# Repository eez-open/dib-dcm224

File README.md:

### Ownership and License
The contributors are listed in CONTRIB.TXT.

Licenses | OSHWA UID
--|--
 | 

### Overview

The EEZ DIB DCM224 Power module features dual sync buck converters based on [LT3763](https://www.analog.com/en/products/lt3763.html) with programmable output voltage, PWM dimming and current limit.

### r3B2 prototype

### Feature list
- On-board STM32F373 MCU
Power input: 48 Vdc (e.g. Mean Well LRS-150F-48)
- Combined max. output power: up to 155 W
- Separate control of each power outputs
- Voltage regulation (CV), 1 – 24 V. Voltage set resolution (_U_SET_): 12-bit, read resolution (_U_MON_): 15-bit
- Current regulation (CC), up to 4.9 A. Current set resolution (_I_SET_): 12-bit, read resolution (_I_MON_): 15-bit
- PWM LED dimming
- MCU generated two counterphase switching frequencies
- On-board power pre-regulator and bias power supply
- Output Enable (_OE_) and Constant Current mode (_CC_) LED indications
- Output LC filter for improved ripple and noise
- On-board 4 mm power output terminals with standard (19.05 mm) pitch
- Pass-thru connector for Vout- coupling with other DIB power modules
- Galvanically isolated SPI bus for communication with [MCU board](https://github.com/eez-open/modular-psu/tree/master/mcu)
- I2C EEPROM for storing board specific configuration and calibration parameters
- Dimensions: 155 x 95 mm, 4-layer PCB
- **CE certified design**

### Firmware repository

https://github.com/eez-open/dib-dcm224-fw  
The firmware download procedure is described in Chapter 13.2 of the [User Manual](https://www.envox.eu/eez-bench-box-3/bb3-user-manual/13-firmware-upgrade/#bb3_man_module_upgrade).

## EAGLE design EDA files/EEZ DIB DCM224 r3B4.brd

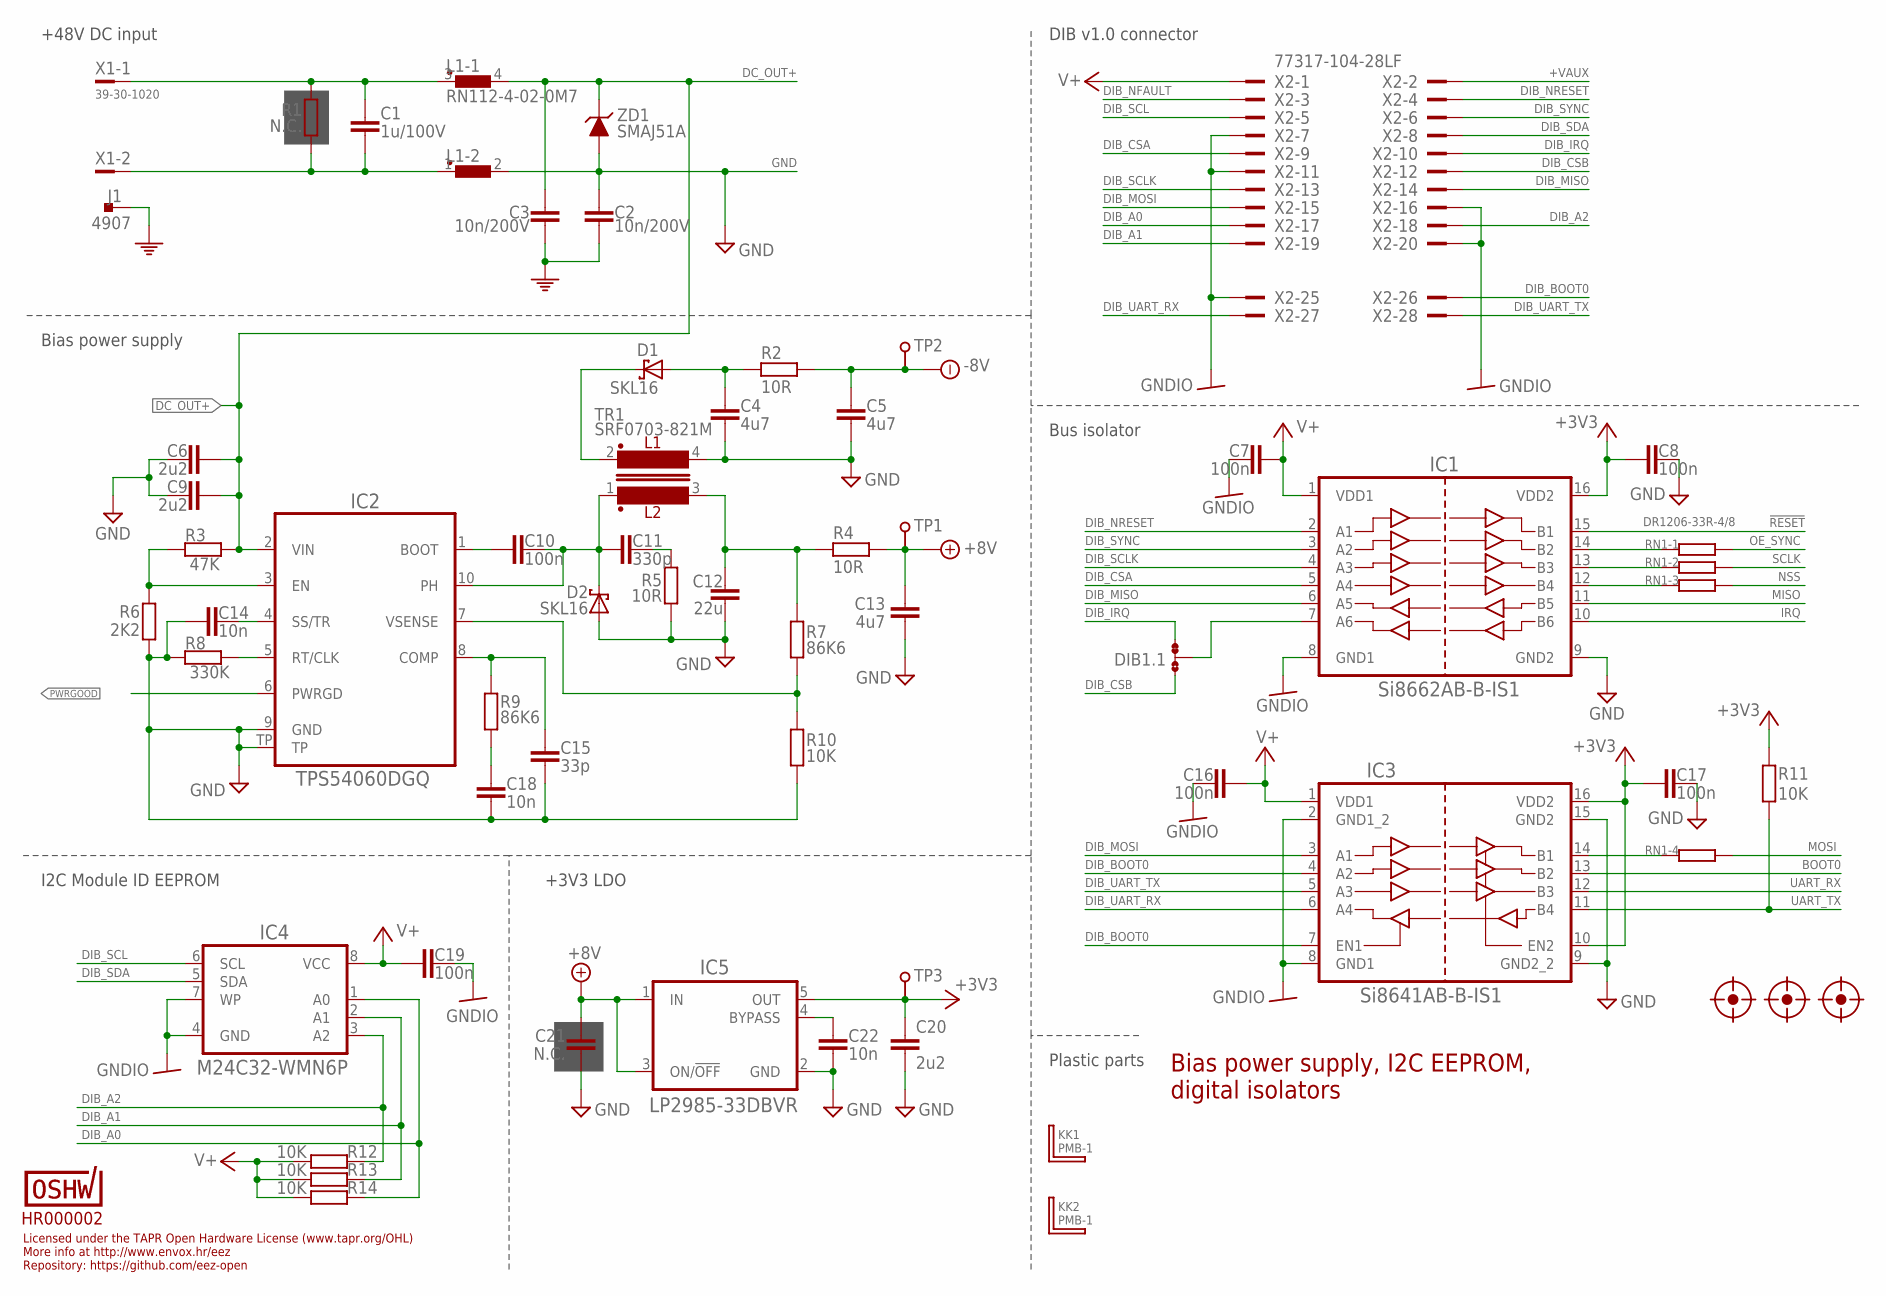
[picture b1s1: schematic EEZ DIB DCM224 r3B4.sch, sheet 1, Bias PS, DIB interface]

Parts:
C1: 1u/100V; C1206
C2, C3: 10n/200V; C1206
C4, C5, C13: 4u7; C1206
C6, C9, C20: 2u2; C1206
C7, C8, C10, C16, C17, C19: 100n; C0603
C11: 330p; C0805
C12: 22u; C1206
C14, C18, C22: 10n; C0805
C15: 33p; C0603
C21: N.C.; C0805
D1, D2: SKL16; SOD123
DIB1.1: JP3-CUT-0805-ROTATED; JP3-0805-CUT2
FM1, FM2, FM3: FIDUCIAL_2; FIDUCIAL_DUAL
IC1: Si8662AB-B-IS1; SOIC-16
IC2: TPS54060DGQ; SOP50P490X110-11N
IC3: Si8641AB-B-IS1; SOIC-16
IC4: M24C32-WMN6P; SOIC127P600X173-8N
IC5: LP2985-33DBVR; SOT95P270X145-5N
J1: 4907; PCB_TAB-4907
KK1, KK2: PMB-1; PCB-MB
L1: RN112-4-02-0M7; RN112
R1: N.C.; R2512
R2, R4, R5: 10R; R0805
R3: 47K; R0805
R6: 2K2; R0805
R7, R9: 86K6; R0805
R8: 330K; R0805
R10, R11, R12, R13, R14: 10K; R0805
RN1: DR1206-33R-4/8; CAY16
TP1, TP2, TP3: TEST-PIN_0.9MM
TR1: SRF0703-821M; SRF0703
U$1: HR000002; CERT-SMALL-SILK
X1: 39-30-1020; MINIFIT_39301020
X2: 77317-104-28LF
ZD1: SMAJ51A; DO214AA

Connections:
!RESET: IC1.15 (B1); also elsewhere on the board
+3V3: C8.2, C17.2, C20.1, IC1.16 (VDD2), IC3.10 (EN2), IC3.16 (VDD2), IC5.5 (OUT), R11.2, TP3.1; also elsewhere on the board
+8V: C13.1, C21.2, IC5.1 (IN), IC5.3 (ON/!OFF), R4.1, TP1.1; also elsewhere on the board
+VAUX: X2.2
-8V: C5.1, R2.1, TP2.1; also elsewhere on the board
BOOT0: IC3.13 (B2); also elsewhere on the board
DC+: C1.2, L1.3 (1), R1.2, X1.1
DC-: C1.1, L1.1, R1.1, X1.2
DC_OUT+: C3.2, C6.1, C9.1, IC2.2 (VIN), L1.4 (2), R3.2, ZD1.C; also elsewhere on the board
DIB_A0: IC4.1 (A0), R14.2, X2.17
DIB_A1: IC4.2 (A1), R13.2, X2.19
DIB_A2: IC4.3 (A2), R12.2, X2.18
DIB_BOOT0: IC3.4 (A2), IC3.7 (EN1), X2.26
DIB_CSA: IC1.5 (A4), X2.9
DIB_CSB: DIB1.1.NO, X2.12
DIB_IRQ: DIB1.1.NC, X2.10
DIB_MISO: IC1.6 (A5), X2.14
DIB_MOSI: IC3.3 (A1), X2.15
DIB_NFAULT: X2.3
DIB_NRESET: IC1.2 (A1), X2.4
DIB_SCL: IC4.6 (SCL), X2.5
DIB_SCLK: IC1.4 (A3), X2.13
DIB_SDA: IC4.5 (SDA), X2.8
DIB_SYNC: IC1.3 (A2), X2.6
DIB_UART_RX: IC3.6 (A4), X2.27
DIB_UART_TX: IC3.5 (A3), X2.28
GND: C2.1, C4.2, C5.2, C6.2, C8.1, C9.2, C12.2, C13.2, C14.2, C15.1, C17.1, C18.1, C20.2, C21.1, C22.1, D2.A, IC1.9 (GND2), IC2.9 (GND), IC2.TP, IC3.9 (GND2_2), IC3.15 (GND2), IC5.2 (GND), L1.2, R5.1, R6.1, R8.1, R10.1, TR1.4, ZD1.A; also elsewhere on the board
GNDIO: C7.2, C16.2, C19.1, IC1.8 (GND1), IC3.2 (GND1_2), IC3.8 (GND1), IC4.4 (GND), IC4.7 (WP), X2.7, X2.11, X2.16, X2.20, X2.25
IRQ: IC1.10 (B6); also elsewhere on the board
MISO: IC1.11 (B5); also elsewhere on the board
MOSI: RN1.5 (2); also elsewhere on the board
unnamed: IC1.14 (B2), RN1.1
unnamed: IC1.13 (B3), RN1.2 (1)
unnamed: IC1.12 (B4), RN1.3 (1)
unnamed: IC3.14 (B1), RN1.4 (1)
unnamed: C22.2, IC5.4 (BYPASS)
unnamed: C4.1, D1.A, R2.2
unnamed: C11.2, R5.2
unnamed: IC2.3 (EN), R3.1, R6.2
unnamed: C14.1, IC2.4 (SS/TR)
unnamed: IC2.5 (RT/CLK), R8.2
unnamed: C15.2, IC2.8 (COMP), R9.2
unnamed: C18.2, R9.1
unnamed: C10.2, IC2.1 (BOOT)
unnamed: IC2.7 (VSENSE), R7.1, R10.2
unnamed: DIB1.1.COM, IC1.7 (A6)
NSS: RN1.6 (2); also elsewhere on the board
OE_SYNC: RN1.8 (2); also elsewhere on the board
PE: C2.2, C3.1, J1.1, J1.2; also elsewhere on the board
PH1: C10.1, C11.1, D2.C, IC2.10 (PH), TR1.1
PWRGOOD: IC2.6 (PWRGD); also elsewhere on the board
SCLK: RN1.7 (2); also elsewhere on the board
UART_RX: IC3.12 (B3); also elsewhere on the board
UART_TX: IC3.11 (B4), R11.1; also elsewhere on the board
V+: C7.1, C16.1, C19.2, IC1.1 (VDD1), IC3.1 (VDD1), IC4.8 (VCC), R12.1, R13.1, R14.1, X2.1
VOUT+: C12.1, R4.2, R7.2, TR1.3
VOUT-: D1.C, TR1.2

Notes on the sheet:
Licensed under the TAPR Open Hardware License (www.tapr.org/OHL)
Repository: https://github.com/eez-open
More info at http://www.envox.hr/eez
I2C Module ID EEPROM
Bias power supply, I2C EEPROM, digital isolators
Plastic parts
Bus isolator
+3V3 LDO
DIB v1.0 connector
Bias power supply
+48V DC input

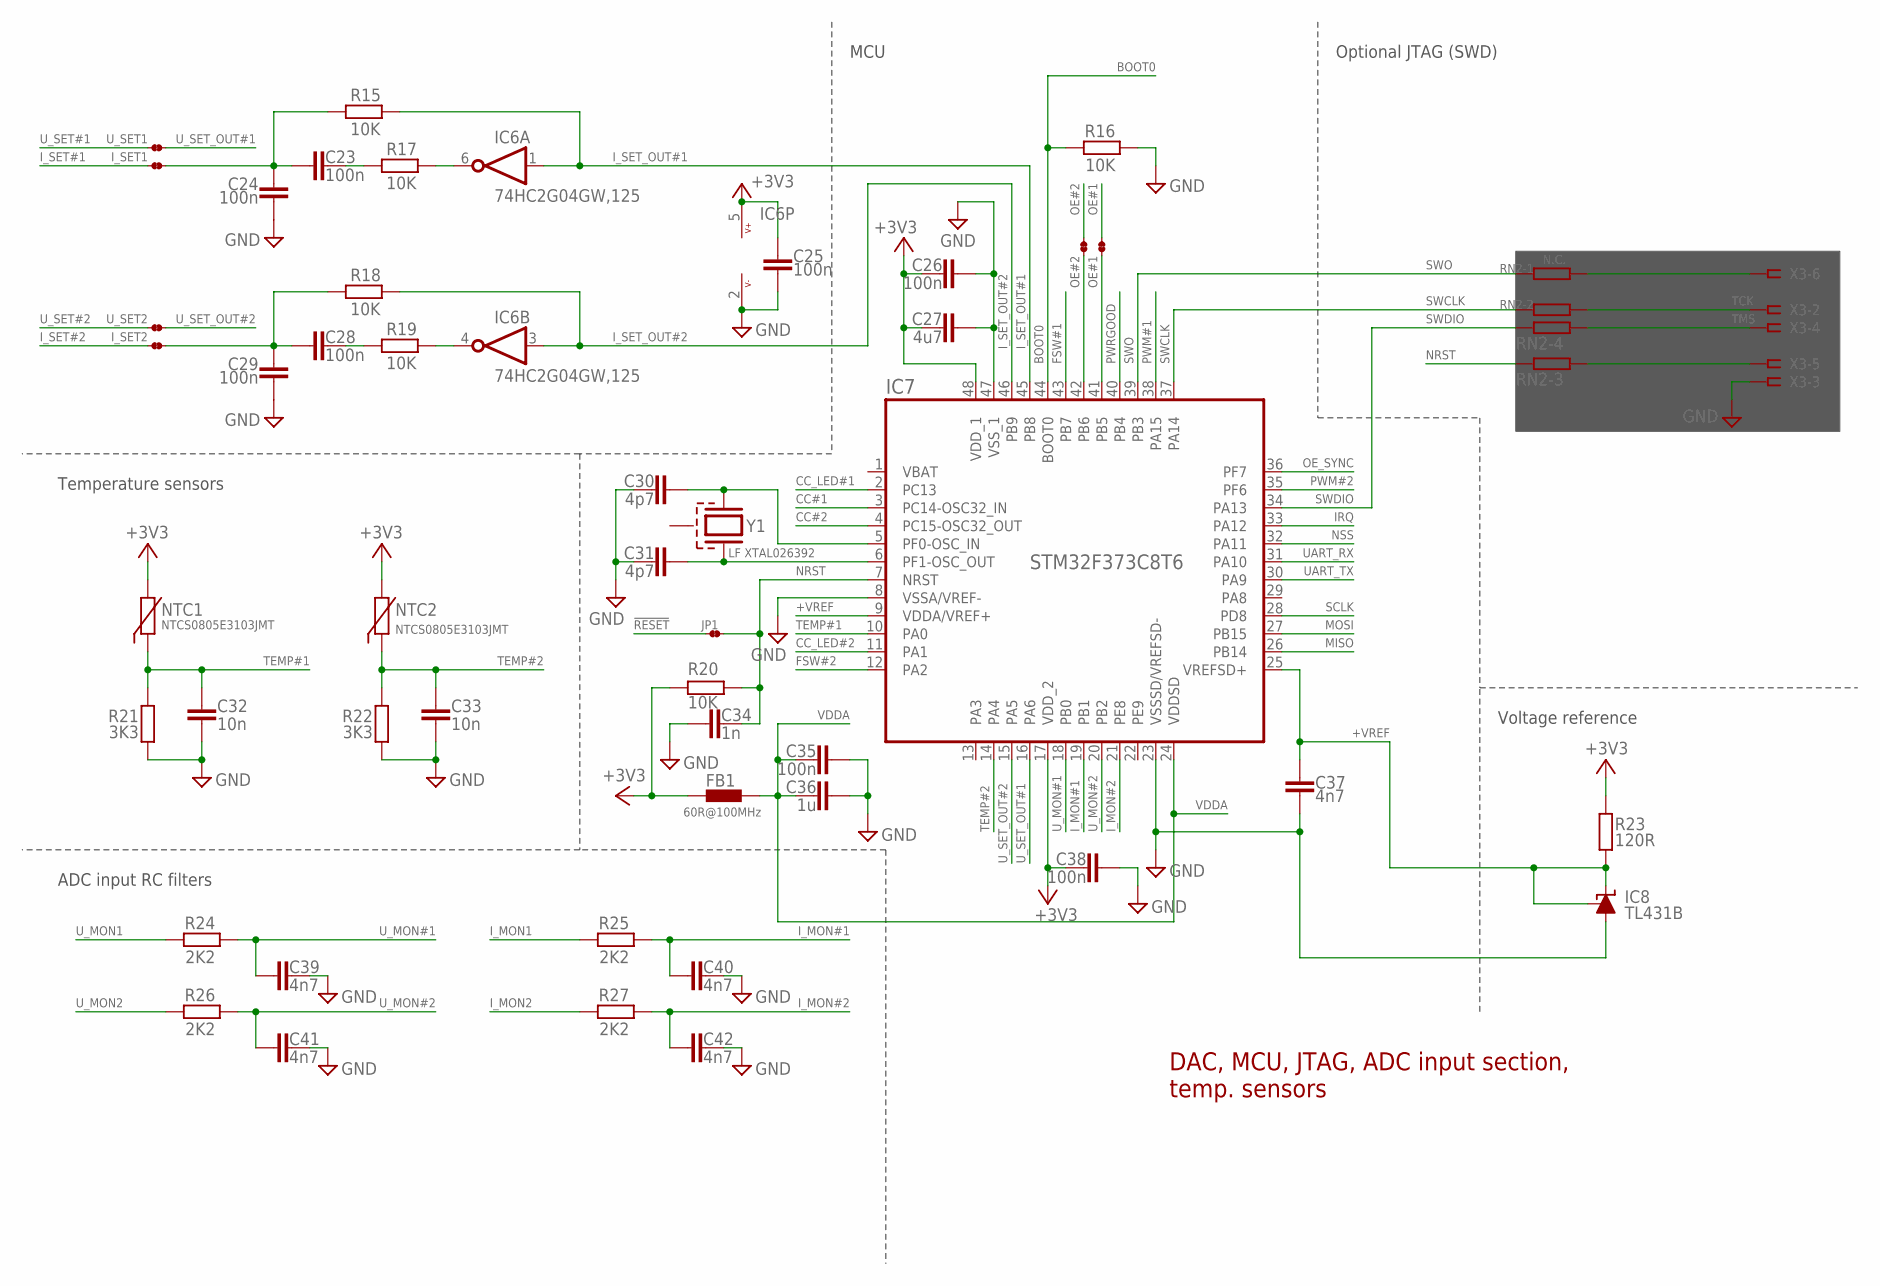
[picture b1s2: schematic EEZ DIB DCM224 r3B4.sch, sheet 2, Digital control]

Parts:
C23, C24, C25, C26, C28, C29, C35, C38: 100n; C0603
C27: 4u7; C1206
C30, C31: 4p7; C0603
C32, C33: 10n; C0805
C34: 1n; C0805
C36: 1u; C0805
C37, C39, C40, C41, C42: 4n7; C0805
FB1: 60R@100MHz; BEAD0603
IC6: 74HC2G04GW,125; SOT65P210X110-6N
IC7: STM32F373C8T6; LQFP-48
IC8: TL431B; SOT103P240X110-3N
I_SET1, I_SET2: JP2-NOCUT
JP1: JP2-NOCUT
NTC1, NTC2: NTCS0805E3103JMT; R_0805
OE#1, OE#2: JP2-NOCUT-0805; JP2-0805-NOCUT
R15, R16, R17, R18, R19, R20: 10K; R0805
R21, R22: 3K3; R0805
R23: 120R; R0805
R24, R25, R26, R27: 2K2; R0805
RN2: N.C.; CAY16
U_SET1, U_SET2: JP2-NOCUT
X3: N.C.; SSW-106-02-S-S
Y1: LF XTAL026392; 12SMX(B)

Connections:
!RESET: JP1.1; also elsewhere on the board
+3V3: C25.1, C26.2, C27.1, C38.2, FB1.P$1 (1), IC6.5 (V+), IC7.17 (VDD_2), IC7.48 (VDD_1), NTC1.1, NTC2.1, R20.1, R23.1; also elsewhere on the board
+VREF: C37.2, IC7.9 (VDDA/VREF+), IC7.25 (VREFSD+), IC8.1 (C), IC8.2 (R), R23.2
BOOT0: IC7.44 (BOOT0), R16.2; also elsewhere on the board
CC#1: IC7.3 (PC14-OSC32_IN); also elsewhere on the board
CC#2: IC7.4 (PC15-OSC32_OUT); also elsewhere on the board
CC_LED#1: IC7.2 (PC13); also elsewhere on the board
CC_LED#2: IC7.11 (PA1); also elsewhere on the board
FSW#1: IC7.43 (PB7); also elsewhere on the board
FSW#2: IC7.12 (PA2); also elsewhere on the board
GND: C24.2, C25.2, C26.1, C27.2, C29.2, C30.1, C31.1, C32.1, C33.1, C34.2, C35.1, C36.1, C37.1, C38.1, C39.1, C40.1, C41.1, C42.1, IC6.2 (V-), IC7.8 (VSSA/VREF-), IC7.23 (VSSSD/VREFSD-), IC7.47 (VSS_1), IC8.3 (A), R16.1, R21.2, R22.2, X3.3; also elsewhere on the board
IRQ: IC7.33 (PA12); also elsewhere on the board
I_MON1: R25.2; also elsewhere on the board
I_MON2: R27.2; also elsewhere on the board
I_MON#1: C40.2, IC7.19 (PB1), R25.1
I_MON#2: C42.2, IC7.21 (PE8), R27.1
I_SET#1: I_SET1.1; also elsewhere on the board
I_SET#2: I_SET2.1; also elsewhere on the board
I_SET_OUT#1: IC6.1 (I), IC7.45 (PB8), R15.2
I_SET_OUT#2: IC6.3 (I), IC7.46 (PB9), R18.2
MISO: IC7.26 (PB14); also elsewhere on the board
MOSI: IC7.27 (PB15); also elsewhere on the board
unnamed: C28.2, R19.1
unnamed: C28.1, C29.1, I_SET2.2, R18.1
unnamed: IC6.4 (O), R19.2
unnamed: RN2.8 (2), X3.6
unnamed: RN2.6 (2), X3.5
unnamed: C23.2, R17.1
unnamed: C23.1, C24.1, I_SET1.2, R15.1
unnamed: IC6.6 (O), R17.2
unnamed: IC7.42 (PB6), OE#2.1
unnamed: IC7.41 (PB5), OE#1.1
NRST: C34.1, IC7.7 (NRST), JP1.2, R20.2, RN2.3 (1)
NSS: IC7.32 (PA11); also elsewhere on the board
OE#1: OE#1.2; also elsewhere on the board
OE#2: OE#2.2; also elsewhere on the board
OE_SYNC: IC7.36 (PF7); also elsewhere on the board
PWM#1: IC7.38 (PA15); also elsewhere on the board
PWM#2: IC7.35 (PF6); also elsewhere on the board
PWRGOOD: IC7.40 (PB4); also elsewhere on the board
RCC_OSC_IN: C30.2, IC7.5 (PF0-OSC_IN), Y1.3 (2)
RCC_OSC_OUT: C31.2, IC7.6 (PF1-OSC_OUT), Y1.1
SCLK: IC7.28 (PD8); also elsewhere on the board
SWCLK: IC7.37 (PA14), RN2.2 (1)
SWDIO: IC7.34 (PA13), RN2.4 (1)
SWO: IC7.39 (PB3), RN2.1
TCK: RN2.7 (2), X3.2
TEMP#1: C32.2, IC7.10 (PA0), NTC1.2, R21.1
TEMP#2: C33.2, IC7.14 (PA4), NTC2.2, R22.1
TMS: RN2.5 (2), X3.4
UART_RX: IC7.31 (PA10); also elsewhere on the board
UART_TX: IC7.30 (PA9); also elsewhere on the board
U_MON1: R24.2; also elsewhere on the board
U_MON2: R26.2; also elsewhere on the board
U_MON#1: C39.2, IC7.18 (PB0), R24.1
U_MON#2: C41.2, IC7.20 (PB2), R26.1
U_SET#1: U_SET1.1; also elsewhere on the board
U_SET#2: U_SET2.1; also elsewhere on the board
U_SET_OUT#1: IC7.16 (PA6), U_SET1.2
U_SET_OUT#2: IC7.15 (PA5), U_SET2.2
VDDA: C35.2, C36.2, FB1.P$2 (2), IC7.24 (VDDSD)

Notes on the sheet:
DAC, MCU, JTAG, ADC input section, temp. sensors
Optional JTAG (SWD)
MCU
Temperature sensors
ADC input RC filters
Voltage reference

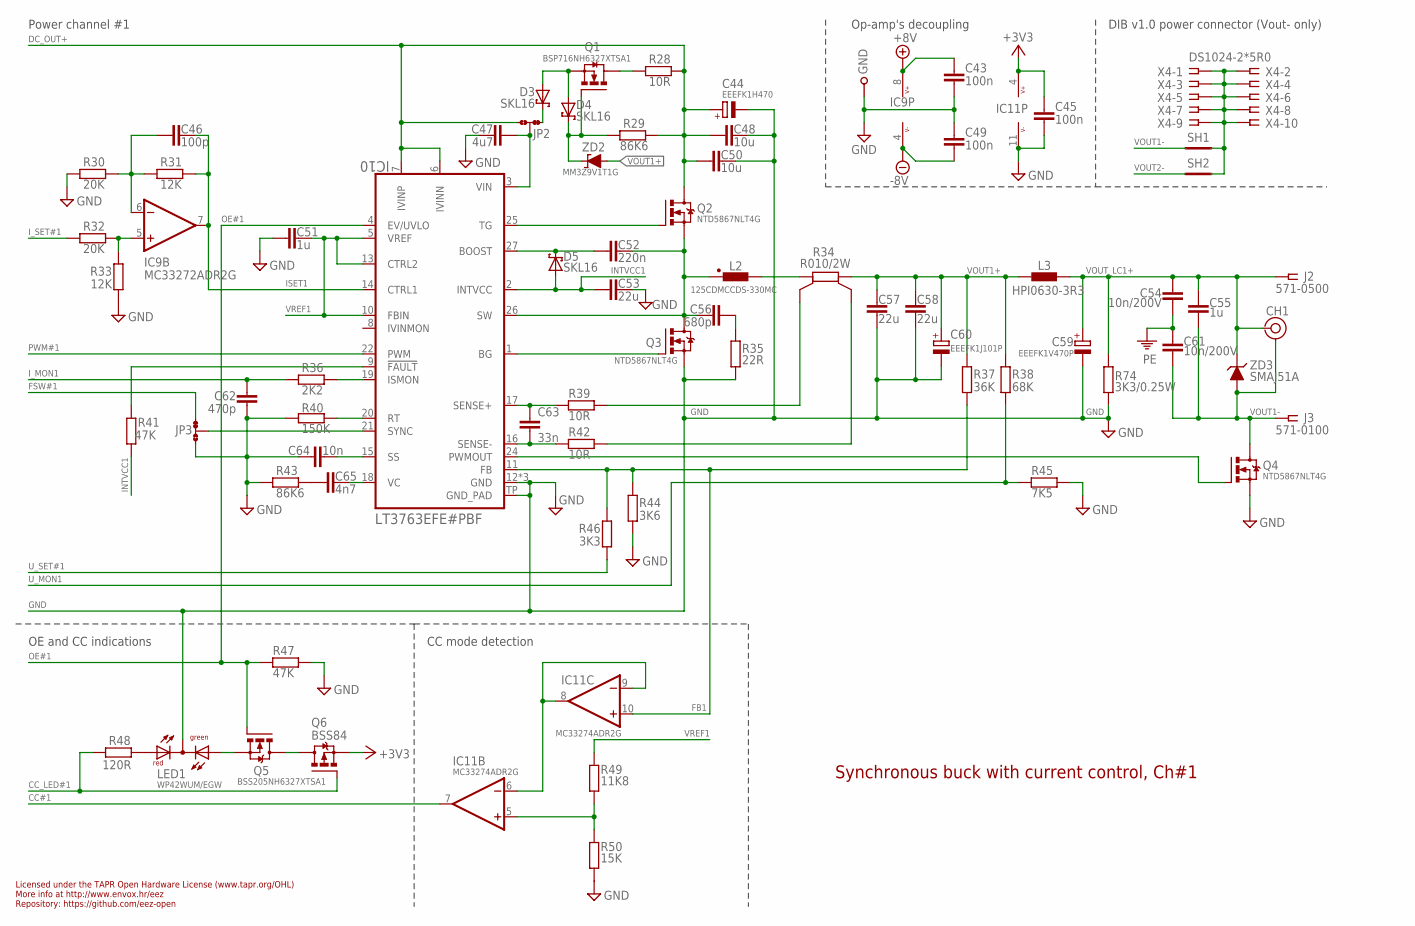
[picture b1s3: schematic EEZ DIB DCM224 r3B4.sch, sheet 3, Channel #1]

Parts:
C43, C45, C49: 100n; C0603
C44: EEEFK1H470; CAPAE830X1050N
C46: 100p; C0805
C47: 4u7; C1206
C48, C50: 10u; C1210
C51, C55: 1u; C0805
C52: 220n; C0805
C53: 22u; C1206
C54, C61: 10n/200V; C1206
C56: 680p; C0805
C57, C58: 22u; C1210
C59: EEEFK1V470P; CAPAE660X610N
C60: EEEFK1J101P; CAPAE1030X1050N
C62: 470p; C0805
C63: 33n; C0805
C64: 10n; C0805
C65: 4n7; C0805
CH1: TEST_POINT-2; TP_1.1MM_2
D3, D4, D5: SKL16; SOD123
GND: TEST-PIN_0.9MM
IC9: MC33272ADR2G; SOIC127P600X173-8N
IC10: LT3763EFE#PBF; LTC_05-08-1663-EB
IC11: MC33274ADR2G; SOIC127P600X175-14N
J2: 571-0500; DELTRON_571
J3: 571-0100; DELTRON_571
JP2, JP3: JP3-CUT-0805-ROTATED; JP3-0805-CUT2
L2: 125CDMCCDS-330MC; 125CDMCC/DS
L3: HPI0630-3R3; COILCRAFT_HPI0630
LED1: WP42WUM/EGW; L-42WUM-1EGWT
Q1: BSP716NH6327XTSA1; SOT223
Q2, Q3, Q4: NTD5867NLT4G; TO252
Q5: BSS205NH6327XTSA1; SOT103P240X110-3N
Q6: BSS84; SOT95P237X112-3N
R28, R39, R42: 10R; R0805
R29, R43: 86K6; R0805
R30, R32: 20K; R0805
R31, R33: 12K; R0805
R34: R010/2W; R_2512-4WIRE
R35: 22R; R1206
R36: 2K2; R0805
R37: 36K; R0805
R38: 68K; R0805
R40: 150K; R0805
R41, R47: 47K; R0805
R44: 3K6; R0805
R45: 7K5; R0805
R46: 3K3; R0805
R48: 120R; R0805
R49: 11K8; R0805
R50: 15K; R0805
R74: 3K3/0.25W; R1206
SH1, SH2: SHORTNOHOLE; SHORT_NOHOLE
X4: DS1024-2*5R0; SSW-105-02-T-D-RA
ZD2: MM3Z9V1T1G; SOD323-W
ZD3: SMAJ51A; DO214AA

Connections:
+3V3: C45.1, IC11.4 (V+), Q6.2 (S); also elsewhere on the board
+8V: C43.1, IC9.8 (V+); also elsewhere on the board
-8V: C49.2, IC9.4 (V-); also elsewhere on the board
BG1: IC10.1 (BG), Q3.1 (G)
CC#1: IC11.7 (OUT); also elsewhere on the board
CC_LED#1: Q6.1 (G), R48.2; also elsewhere on the board
DC_OUT+: C44.+, C48.1, C50.1, IC10.6 (IVINN), IC10.7 (IVINP), JP2.NO, Q2.3 (D), R28.1, R29.1; also elsewhere on the board
FB1: IC10.11 (FB), IC11.10 (+IN), R37.1, R44.2, R46.2
FSW#1: JP3.NC; also elsewhere on the board
GND: C43.2, C44.-, C45.2, C47.2, C48.2, C49.1, C50.2, C51.2, C53.2, C57.2, C58.2, C59.2 (-), C60.-, C62.1, C64.1, GND.1, IC10.12 (GND), IC10.23 (GND), IC10.28 (GND), IC10.TP (GND_PAD), IC11.11 (V-), JP3.NO, LED1.CC (C), Q3.2 (S), Q4.2 (S), R30.1, R33.1, R35.1, R40.1, R43.1, R44.1, R45.1, R47.2, R50.1, R74.1; also elsewhere on the board
INTVCC1: C53.1, D5.A, IC10.2 (INTVCC), R41.2
ISET1: C46.1, IC9.7 (OUT), IC10.14 (CTRL1), R31.2
I_MON1: C62.2, R36.1; also elsewhere on the board
I_SET#1: R32.1; also elsewhere on the board
LOUT1: L2.2, R34.1
unnamed: IC10.21 (SYNC), JP3.COM
unnamed: D3.C, JP2.NC
unnamed: Q5.3 (D), Q6.3 (D)
unnamed: R34.1S, R39.2
unnamed: IC10.20 (RT), R40.2
unnamed: LED1.RED (AR), R48.1
unnamed: C64.2, IC10.15 (SS)
unnamed: C65.1, R43.2
unnamed: C65.2, IC10.18 (VC)
unnamed: R34.2S, R42.2
unnamed: C56.2, R35.2
unnamed: IC10.9 (!FAULT), R41.1
unnamed: C52.1, D5.C, IC10.27 (BOOST)
unnamed: D4.C, Q1.1 (G), R29.2, ZD2.C
unnamed: LED1.GREEN (AG), Q5.2 (S)
unnamed: C47.1, IC10.3 (VIN), JP2.COM
unnamed: D3.A, D4.A, Q1.3 (S)
unnamed: IC10.19 (ISMON), R36.2
unnamed: SH1.2 (GND_B), SH2.2 (GND_B), X4.1, X4.2, X4.3, X4.4, X4.5, X4.6, X4.7, X4.8, X4.9, X4.10
unnamed: IC11.5 (+IN), R49.1, R50.2
unnamed: IC11.6 (-IN), IC11.8 (OUT), IC11.9 (-IN)
unnamed: IC9.5 (+IN), R32.2, R33.2
unnamed: C46.2, IC9.6 (-IN), R30.2, R31.1
unnamed: IC10.24 (PWMOUT), Q4.1 (G)
OE#1: IC10.4 (EV/UVLO), Q5.1 (G), R47.1; also elsewhere on the board
PE: C54.1, C61.1; also elsewhere on the board
PWM#1: IC10.22 (PWM); also elsewhere on the board
Q1D: Q1.2 (D), Q1.4 (D), R28.2
SENSE1+: C63.1, IC10.17 (SENSE+), R39.1
SENSE1-: C63.2, IC10.16 (SENSE-), R42.1
SW1: C52.2, C56.1, IC10.26 (SW), L2.1, Q2.2 (S), Q3.3 (D)
TG1: IC10.25 (TG), Q2.1 (G)
U_MON1: R38.1, R45.2; also elsewhere on the board
U_SET#1: R46.1; also elsewhere on the board
VOUT1+: C57.1, C58.1, C60.+, L3.1, R34.2, R37.2, R38.2, ZD2.A
VOUT1-: C55.2, C61.2, CH1.GND, J3.1, J3.1.1, Q4.3 (D), SH1.1 (GND_A), ZD3.A
VOUT2-: SH2.1 (GND_A); also elsewhere on the board
VOUT_LC1+: C54.2, C55.1, C59.1 (+), CH1.TIP, J2.1, J2.1.1, L3.2, R74.2, ZD3.C
VREF1: C51.1, IC10.5 (VREF), IC10.10 (FBIN), IC10.13 (CTRL2), R49.2

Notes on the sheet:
Licensed under the TAPR Open Hardware License (www.tapr.org/OHL)
Repository: https://github.com/eez-open
More info at http://www.envox.hr/eez
Power channel #1
CC mode detection
DIB v1.0 power connector (Vout- only)
Op-amp's decoupling
OE and CC indications
Synchronous buck with current control, Ch#1

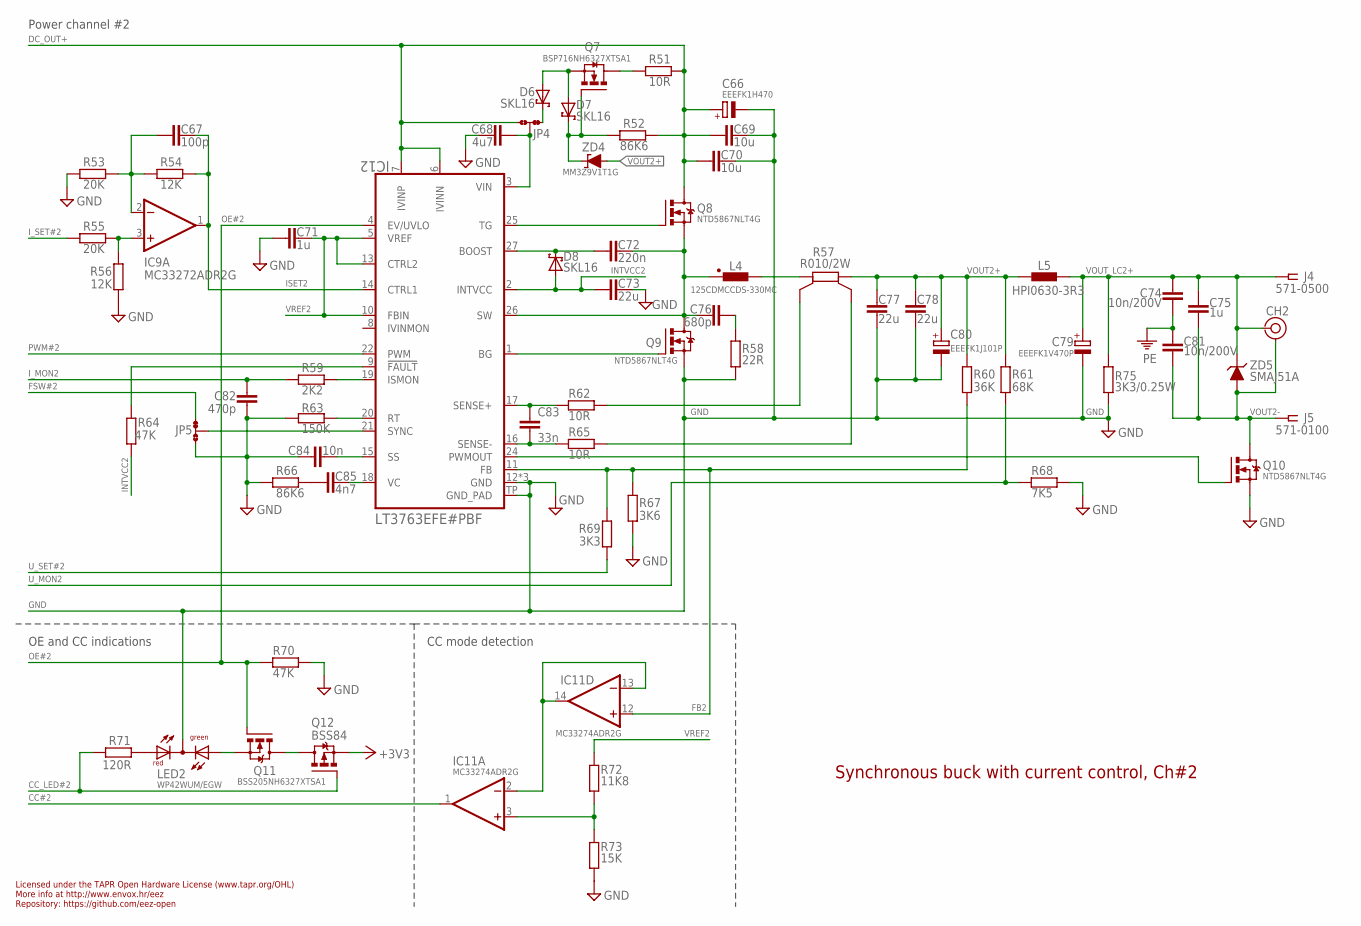
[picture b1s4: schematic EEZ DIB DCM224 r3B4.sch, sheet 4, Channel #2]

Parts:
C66: EEEFK1H470; CAPAE830X1050N
C67: 100p; C0805
C68: 4u7; C1206
C69, C70: 10u; C1210
C71, C75: 1u; C0805
C72: 220n; C0805
C73: 22u; C1206
C74, C81: 10n/200V; C1206
C76: 680p; C0805
C77, C78: 22u; C1210
C79: EEEFK1V470P; CAPAE660X610N
C80: EEEFK1J101P; CAPAE1030X1050N
C82: 470p; C0805
C83: 33n; C0805
C84: 10n; C0805
C85: 4n7; C0805
CH2: TEST_POINT-2; TP_1.1MM_2
D6, D7, D8: SKL16; SOD123
IC9: MC33272ADR2G; SOIC127P600X173-8N
IC11: MC33274ADR2G; SOIC127P600X175-14N
IC12: LT3763EFE#PBF; LTC_05-08-1663-EB
J4: 571-0500; DELTRON_571
J5: 571-0100; DELTRON_571
JP4, JP5: JP3-CUT-0805-ROTATED; JP3-0805-CUT2
L4: 125CDMCCDS-330MC; 125CDMCC/DS
L5: HPI0630-3R3; COILCRAFT_HPI0630
LED2: WP42WUM/EGW; L-42WUM-1EGWT
Q7: BSP716NH6327XTSA1; SOT223
Q8, Q9, Q10: NTD5867NLT4G; TO252
Q11: BSS205NH6327XTSA1; SOT103P240X110-3N
Q12: BSS84; SOT95P237X112-3N
R51, R62, R65: 10R; R0805
R52, R66: 86K6; R0805
R53, R55: 20K; R0805
R54, R56: 12K; R0805
R57: R010/2W; R_2512-4WIRE
R58: 22R; R1206
R59: 2K2; R0805
R60: 36K; R0805
R61: 68K; R0805
R63: 150K; R0805
R64, R70: 47K; R0805
R67: 3K6; R0805
R68: 7K5; R0805
R69: 3K3; R0805
R71: 120R; R0805
R72: 11K8; R0805
R73: 15K; R0805
R75: 3K3/0.25W; R1206
ZD4: MM3Z9V1T1G; SOD323-W
ZD5: SMAJ51A; DO214AA

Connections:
+3V3: Q12.2 (S); also elsewhere on the board
BG2: IC12.1 (BG), Q9.1 (G)
CC#2: IC11.1 (OUT); also elsewhere on the board
CC_LED#2: Q12.1 (G), R71.2; also elsewhere on the board
DC_OUT+: C66.+, C69.1, C70.1, IC12.6 (IVINN), IC12.7 (IVINP), JP4.NO, Q8.3 (D), R51.1, R52.1; also elsewhere on the board
FB2: IC11.12 (+IN), IC12.11 (FB), R60.1, R67.2, R69.2
FSW#2: JP5.NC; also elsewhere on the board
GND: C66.-, C68.2, C69.2, C70.2, C71.2, C73.2, C77.2, C78.2, C79.2 (-), C80.-, C82.1, C84.1, IC12.12 (GND), IC12.23 (GND), IC12.28 (GND), IC12.TP (GND_PAD), JP5.NO, LED2.CC (C), Q9.2 (S), Q10.2 (S), R53.1, R56.1, R58.1, R63.1, R66.1, R67.1, R68.1, R70.2, R73.1, R75.1; also elsewhere on the board
INTVCC2: C73.1, D8.A, IC12.2 (INTVCC), R64.2
ISET2: C67.1, IC9.1 (OUT), IC12.14 (CTRL1), R54.2
I_MON2: C82.2, R59.1; also elsewhere on the board
I_SET#2: R55.1; also elsewhere on the board
LOUT2: L4.2, R57.1
unnamed: LED2.RED (AR), R71.1
unnamed: IC12.21 (SYNC), JP5.COM
unnamed: IC12.20 (RT), R63.2
unnamed: C84.2, IC12.15 (SS)
unnamed: C85.1, R66.2
unnamed: C85.2, IC12.18 (VC)
unnamed: IC12.9 (!FAULT), R64.1
unnamed: R57.1S, R62.2
unnamed: R57.2S, R65.2
unnamed: C76.2, R58.2
unnamed: C72.1, D8.C, IC12.27 (BOOST)
unnamed: IC12.19 (ISMON), R59.2
unnamed: Q11.3 (D), Q12.3 (D)
unnamed: LED2.GREEN (AG), Q11.2 (S)
unnamed: D7.C, Q7.1 (G), R52.2, ZD4.C
unnamed: C68.1, IC12.3 (VIN), JP4.COM
unnamed: D6.A, D7.A, Q7.3 (S)
unnamed: D6.C, JP4.NC
unnamed: IC11.2 (-IN), IC11.13 (-IN), IC11.14 (OUT)
unnamed: IC11.3 (+IN), R72.1, R73.2
unnamed: C67.2, IC9.2 (-IN), R53.2, R54.1
unnamed: IC9.3 (+IN), R55.2, R56.2
unnamed: IC12.24 (PWMOUT), Q10.1 (G)
OE#2: IC12.4 (EV/UVLO), Q11.1 (G), R70.1; also elsewhere on the board
PE: C74.1, C81.1; also elsewhere on the board
PWM#2: IC12.22 (PWM); also elsewhere on the board
Q1D1: Q7.2 (D), Q7.4 (D), R51.2
SENSE1+1: C83.1, IC12.17 (SENSE+), R62.1
SENSE1-1: C83.2, IC12.16 (SENSE-), R65.1
SW2: C72.2, C76.1, IC12.26 (SW), L4.1, Q8.2 (S), Q9.3 (D)
TG2: IC12.25 (TG), Q8.1 (G)
U_MON2: R61.1, R68.2; also elsewhere on the board
U_SET#2: R69.1; also elsewhere on the board
VOUT2+: C77.1, C78.1, C80.+, L5.1, R57.2, R60.2, R61.2, ZD4.A
VOUT2-: C75.2, C81.2, CH2.GND, J5.1, J5.1.1, Q10.3 (D), ZD5.A; also elsewhere on the board
VOUT_LC2+: C74.2, C75.1, C79.1 (+), CH2.TIP, J4.1, J4.1.1, L5.2, R75.2, ZD5.C
VREF2: C71.1, IC12.5 (VREF), IC12.10 (FBIN), IC12.13 (CTRL2), R72.2

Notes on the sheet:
Licensed under the TAPR Open Hardware License (www.tapr.org/OHL)
Repository: https://github.com/eez-open
More info at http://www.envox.hr/eez
CC mode detection
OE and CC indications
Power channel #2
Synchronous buck with current control, Ch#2

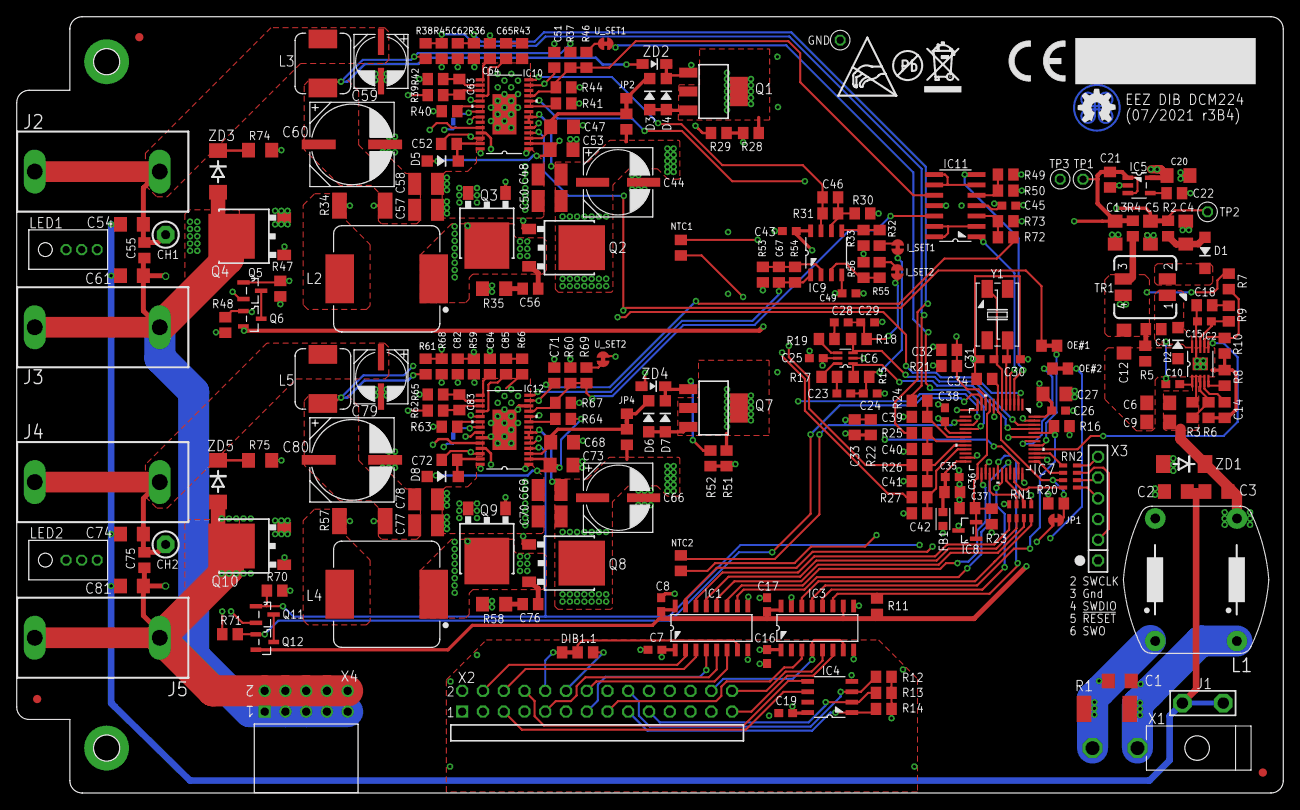
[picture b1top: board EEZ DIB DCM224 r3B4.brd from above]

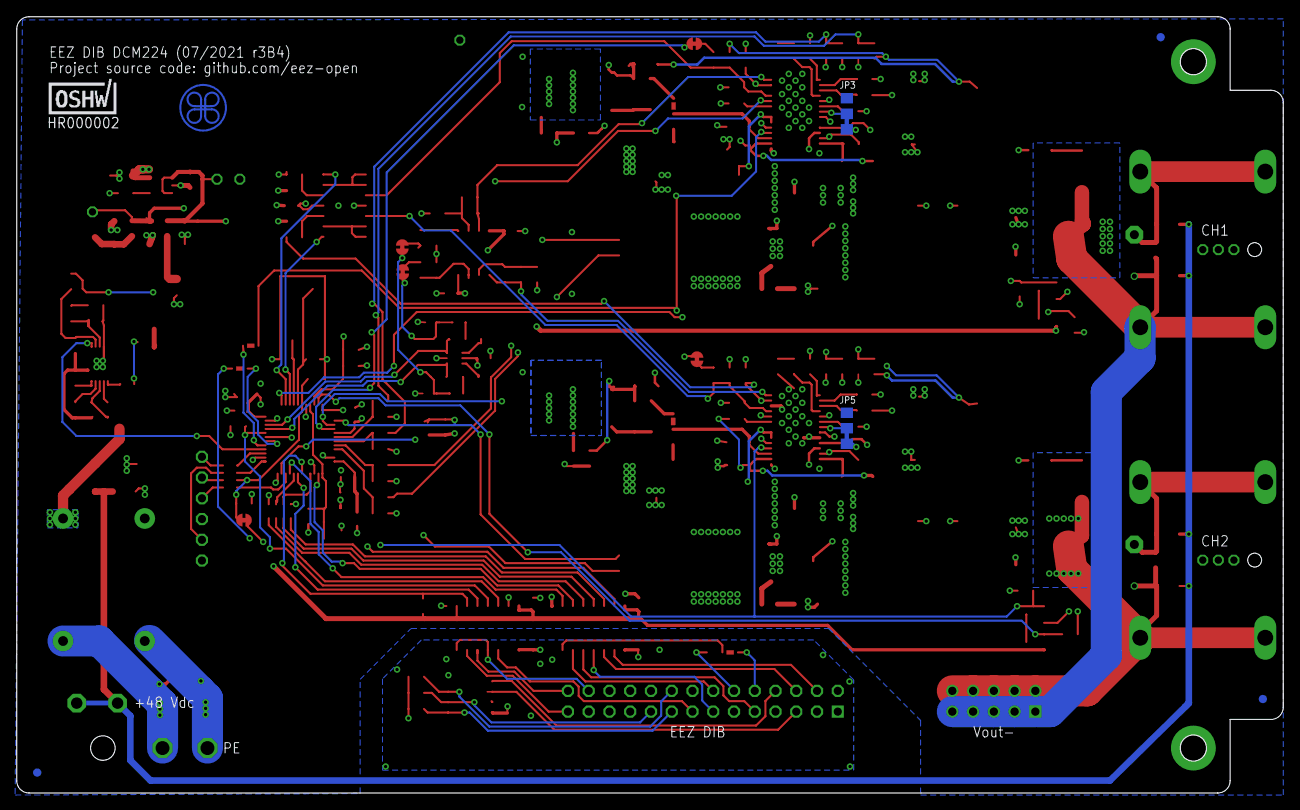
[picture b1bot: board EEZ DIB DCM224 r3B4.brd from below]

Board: 4 copper layers, 155.0 x 95.0 mm, 251 parts (4 on the bottom side), 178 nets.

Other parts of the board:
EEZ_SIGNATURE: SIGNATURESMALL; SIGNATURE_5MM
U$2: RECYCLE_BIN1/8
U$3: CE_5MM
U$4: ESD_SYMBOL
U$7: PB_SMALL

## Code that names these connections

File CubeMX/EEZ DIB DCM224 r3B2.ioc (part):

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Mcu.Name=STM32F373C(8-B-C)Tx
Mcu.Package=LQFP48
Mcu.UserName=STM32F373C8Tx
PA0.GPIOParameters=GPIO_Label
PA0.GPIO_Label=TEMP\#1
PA0.Mode=IN0
PA0.Signal=ADC1_IN0
PA1.GPIOParameters=GPIO_Label
PA1.GPIO_Label=CC_LED\#2
PA1.Signal=GPIO_Output
PA10.Mode=Asynchronous
PA10.Signal=USART1_RX
PA11.GPIOParameters=GPIO_Label
PA11.GPIO_Label=DIB_CSA
PA11.Mode=NSS_Signal_Hard_Input
PA11.Signal=SPI2_NSS
PA12.GPIOParameters=GPIO_Label
PA12.GPIO_Label=DIB_IRQ
PA12.Signal=GPIO_Output
PA13.Mode=Trace_Asynchronous_SW
PA13.Signal=SYS_JTMS-SWDIO
PA14.Mode=Trace_Asynchronous_SW
PA14.Signal=SYS_JTCK-SWCLK
PA15.GPIOParameters=GPIO_Label
PA15.GPIO_Label=PWM\#1
PA15.Signal=GPIO_Output
PA2.GPIOParameters=GPIO_Label
PA2.GPIO_Label=FSW\#2
PA2.Signal=S_TIM19_CH3
PA4.GPIOParameters=GPIO_Label
PA4.GPIO_Label=TEMP\#2
PA4.Mode=IN4
PA4.Signal=ADC1_IN4
PA5.GPIOParameters=GPIO_Label
PA5.GPIO_Label=U_SET\#2
PA5.Signal=COMP_DAC12_group
PA6.GPIOParameters=GPIO_Label
PA6.GPIO_Label=U_SET\#1
PA6.Signal=COMP_DAC21_group
PA9.Mode=Asynchronous
PA9.Signal=USART1_TX
PB0.GPIOParameters=GPIO_Label
PB0.GPIO_Label=U_MON\#1
PB0.Mode=IN6-Single-Ended zero reference
PB0.Signal=SDADC1_AIN6P
PB1.GPIOParameters=GPIO_Label
PB1.GPIO_Label=I_MON\#1
PB1.Mode=IN5-Single-Ended zero reference
PB1.Signal=SDADC1_AIN5P
PB14.GPIOParameters=GPIO_Label
PB14.GPIO_Label=DIB_MISO
PB14.Mode=Full_Duplex_Slave
PB14.Signal=SPI2_MISO
PB15.GPIOParameters=GPIO_Label
PB15.GPIO_Label=DIB_MOSI
PB15.Mode=Full_Duplex_Slave
PB15.Signal=SPI2_MOSI
PB2.GPIOParameters=GPIO_Label
PB2.GPIO_Label=U_MON\#2
PB2.Mode=IN4-Single-Ended zero reference
PB2.Signal=SDADC1_AIN4P
PB3.Mode=Trace_Asynchronous_SW
PB3.Signal=SYS_JTDO-TRACESWO
PB4.GPIOParameters=GPIO_PuPd,GPIO_Label,GPIO_ModeDefaultEXTI
PB4.GPIO_Label=PWRGOOD
PB4.GPIO_ModeDefaultEXTI=GPIO_MODE_IT_RISING_FALLING
PB4.GPIO_PuPd=GPIO_PULLUP
PB4.Signal=GPXTI4
PB5.GPIOParameters=GPIO_Label
PB5.GPIO_Label=OE\#1
PB5.Signal=GPIO_Output
PB6.GPIOParameters=GPIO_Label
PB6.GPIO_Label=OE\#2
PB6.Signal=GPIO_Output
PB7.GPIOParameters=GPIO_Label
PB7.GPIO_Label=FSW\#1
PB7.Signal=S_TIM19_CH2
PB8.GPIOParameters=GPIO_Label
PB8.GPIO_Label=I_SET\#1
PB8.Signal=S_TIM16_CH1
PB9.GPIOParameters=GPIO_Label
PB9.GPIO_Label=I_SET\#2
PB9.Signal=S_TIM17_CH1
PC13.GPIOParameters=GPIO_Label
PC13.GPIO_Label=CC_LED\#1
PC13.Signal=GPIO_Output
PC14-OSC32_IN.GPIOParameters=GPIO_Label,GPIO_ModeDefaultEXTI
PC14-OSC32_IN.GPIO_Label=CC\#1
PC14-OSC32_IN.GPIO_ModeDefaultEXTI=GPIO_MODE_IT_RISING_FALLING
PC14-OSC32_IN.Signal=GPXTI14
PC15-OSC32_OUT.GPIOParameters=GPIO_Label,GPIO_ModeDefaultEXTI
PC15-OSC32_OUT.GPIO_Label=CC\#2
PC15-OSC32_OUT.GPIO_ModeDefaultEXTI=GPIO_MODE_IT_RISING_FALLING
PC15-OSC32_OUT.Signal=GPXTI15
PD8.GPIOParameters=GPIO_Label
PD8.GPIO_Label=DIB_SCK
PD8.Mode=Full_Duplex_Slave
PD8.Signal=SPI2_SCK
PE8.GPIOParameters=GPIO_Label
PE8.GPIO_Label=I_MON\#2
PE8.Mode=IN8-Single-Ended zero reference
PE8.Signal=SDADC1_AIN8P
PF6.GPIOParameters=GPIO_Label
PF6.GPIO_Label=PWM\#2
PF6.Signal=GPIO_Output
PF7.GPIOParameters=GPIO_Label
PF7.GPIO_Label=DIB_SYNC
PF7.Signal=GPXTI7
RCC.HSEPLLFreq_Value=8000000
RCC.HSE_VALUE=16000000
RCC.SYSCLKFreq_VALUE=64000000
RCC.SYSCLKSource=RCC_SYSCLKSOURCE_PLLCLK
board=custom

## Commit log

2021-04-16 licenses logo, mechanical
2021-04-17 readme.md update
2021-04-17 osl label added
2021-04-20 OSHWA UID

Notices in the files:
parts and their libraries:
EEZ_DIB: This work is licensed under the TAPR Open Hardware License.
